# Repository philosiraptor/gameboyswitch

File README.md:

# gameboyswitch
I added joycons to a gameboy advanced sp
if you actually build this let me know.
software component is written in java (SIGH I KNOW)
you will need to get java up and running on a pi zero, its a pain in the butt. 
oh and for some reason the joycons will disconnect if wifi on the pi is enabled,
youll want to run the pi headless over usb (google it)

also you can just order from pcbway to get the board
https://www.pcbway.com/project/shareproject/ground_boi_signal.html

heres a huge iso you can download, burn it with rufus/balena/ idk a tuna sandwich
https://drive.google.com/file/d/150eEt6jt2sRTaDK3TDJbanNfYEL_4Ezm/view?usp=sharing

these instructions are intentionally vauge because you should not build this.

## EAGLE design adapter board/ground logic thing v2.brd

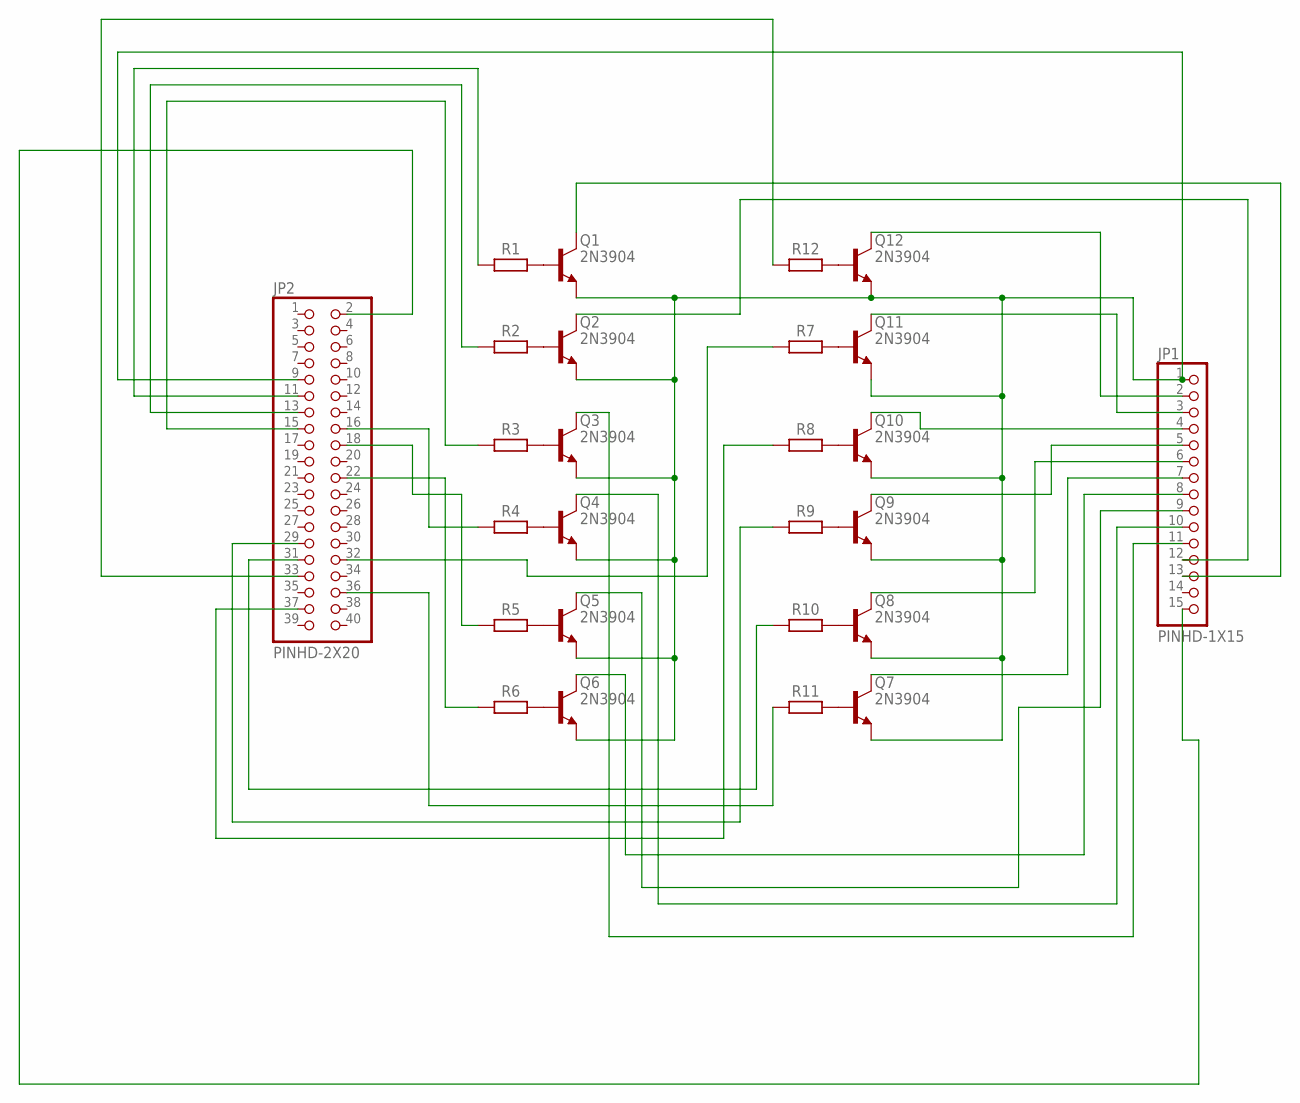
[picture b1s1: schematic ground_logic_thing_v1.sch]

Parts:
JP1: PINHD-1X15; 1X15
JP2: PINHD-2X20; 2X20
Q1, Q2, Q3, Q4, Q5, Q6, Q7, Q8, Q9, Q10, Q11, Q12: 2N3904; TO92
R1, R2, R3, R4, R5, R6, R7, R8, R9, R10, R11, R12: R_AXIAL-7.2MM-PITCH; RESAD724W46L381D178B

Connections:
unnamed: Q1.2 (B), R1.2
unnamed: Q2.2 (B), R2.2
unnamed: Q3.2 (B), R3.2
unnamed: Q4.2 (B), R4.2
unnamed: Q5.2 (B), R5.2
unnamed: Q6.2 (B), R6.2
unnamed: Q11.2 (B), R7.2
unnamed: Q10.2 (B), R8.2
unnamed: Q9.2 (B), R9.2
unnamed: Q8.2 (B), R10.2
unnamed: Q7.2 (B), R11.2
unnamed: Q12.2 (B), R12.2
unnamed: JP1.1, JP2.9, Q1.1 (E), Q2.1 (E), Q3.1 (E), Q4.1 (E), Q5.1 (E), Q6.1 (E), Q7.1 (E), Q8.1 (E), Q9.1 (E), Q10.1 (E), Q11.1 (E), Q12.1 (E)
unnamed: JP2.11, R1.1
unnamed: JP2.13, R2.1
unnamed: JP2.15, R3.1
unnamed: JP2.16, R4.1
unnamed: JP2.18, R5.1
unnamed: JP2.22, R6.1
unnamed: JP2.36, R11.1
unnamed: JP2.31, R10.1
unnamed: JP2.29, R9.1
unnamed: JP2.37, R8.1
unnamed: JP2.32, R7.1
unnamed: JP2.33, R12.1
unnamed: JP1.15, JP2.2
unnamed: JP1.2, Q12.3 (C)
unnamed: JP1.3, Q11.3 (C)
unnamed: JP1.4, Q10.3 (C)
unnamed: JP1.5, Q9.3 (C)
unnamed: JP1.6, Q8.3 (C)
unnamed: JP1.7, Q7.3 (C)
unnamed: JP1.8, Q6.3 (C)
unnamed: JP1.9, Q5.3 (C)
unnamed: JP1.10, Q4.3 (C)
unnamed: JP1.11, Q3.3 (C)
unnamed: JP1.12, Q2.3 (C)
unnamed: JP1.13, Q1.3 (C)

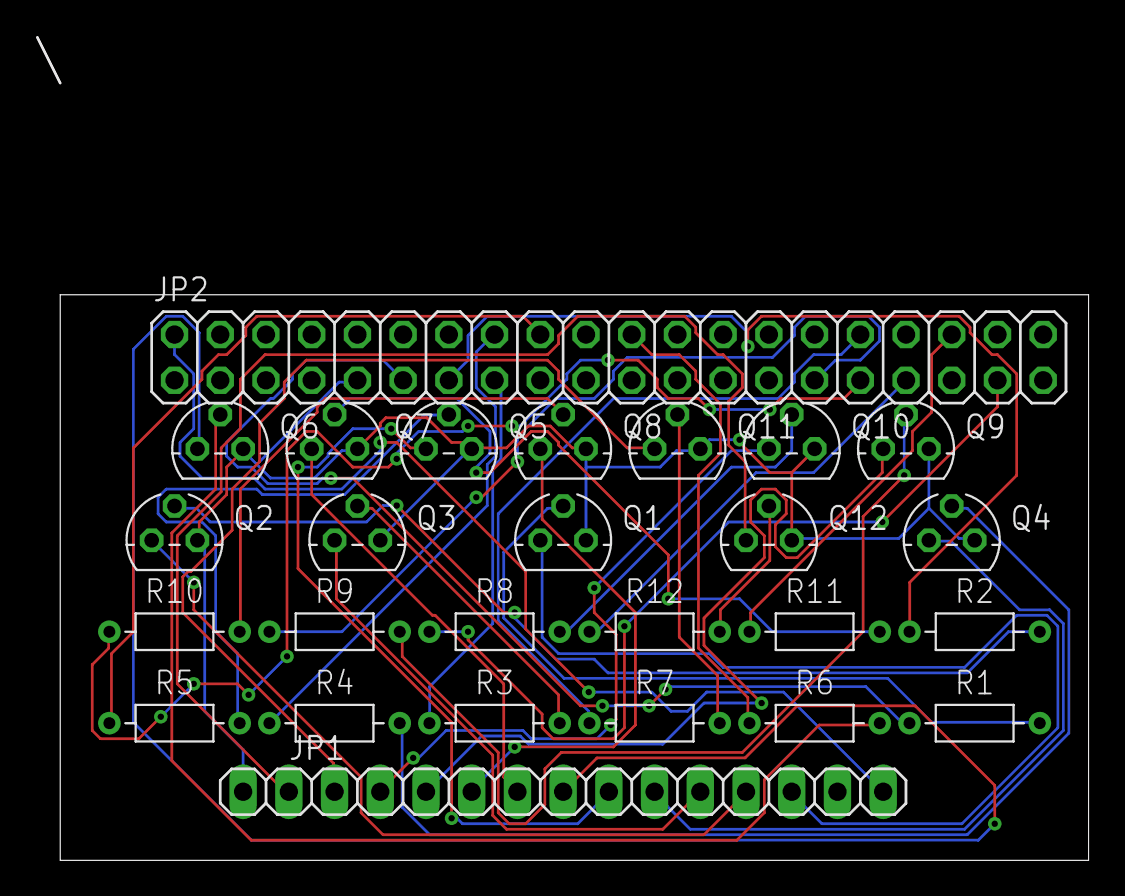
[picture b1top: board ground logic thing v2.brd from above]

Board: 2 copper layers, 58.3 x 45.6 mm, 26 parts (0 on the bottom side), 38 nets.

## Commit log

2021-10-27 initial
    this is the app that runs on the raspberry pi
2021-10-27 additional init
    all the other stuff
